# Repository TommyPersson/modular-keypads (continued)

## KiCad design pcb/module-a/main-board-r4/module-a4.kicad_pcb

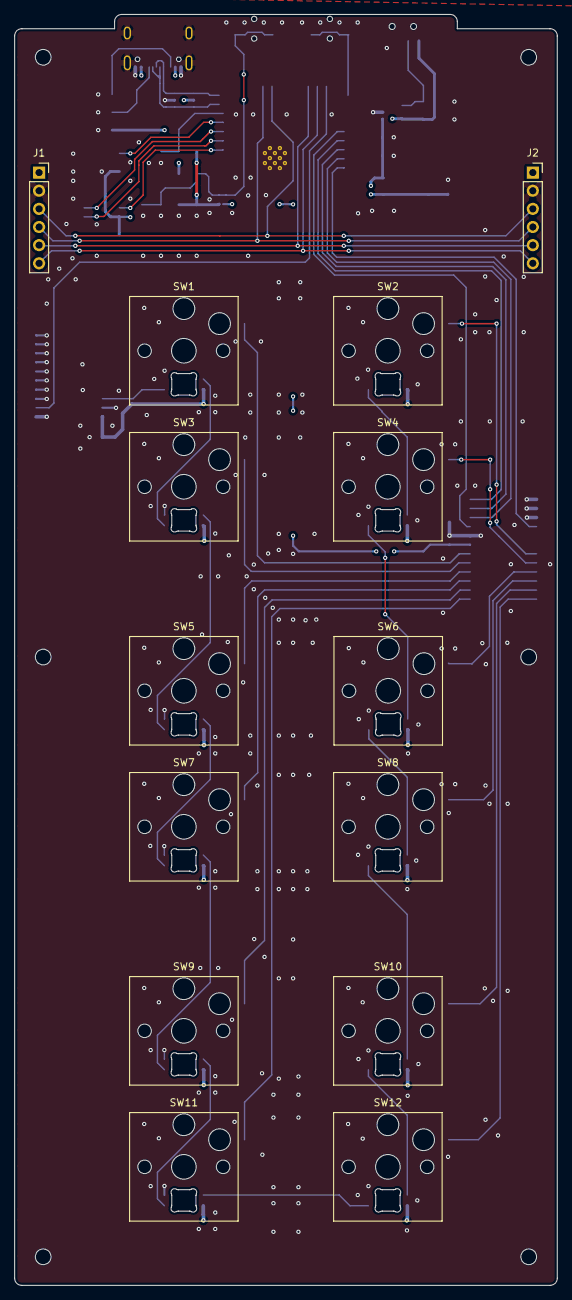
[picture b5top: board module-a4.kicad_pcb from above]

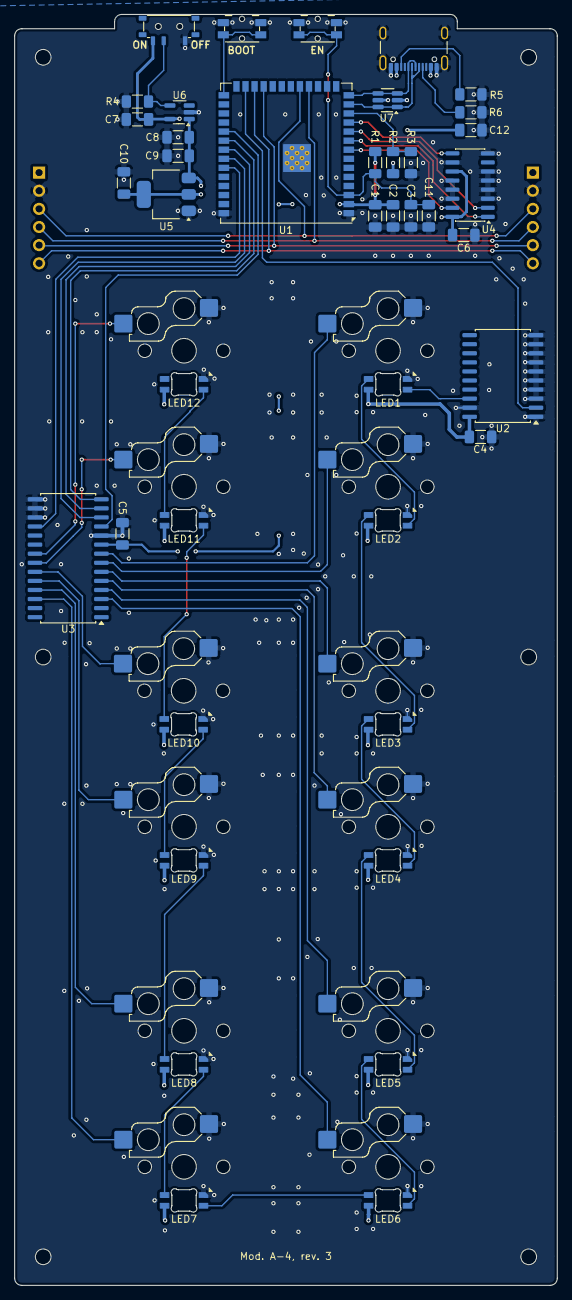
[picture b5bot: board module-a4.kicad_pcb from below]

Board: 4 copper layers, 76.0 x 178.0 mm, 61 parts (41 on the bottom side), 50 nets.

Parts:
C1, C10: 22uF; C_1206_3216Metric_Pad1.33x1.80mm_HandSolder
C2, C4, C5, C6, C7, C8, C11, C12: 0.1uF; C_1206_3216Metric_Pad1.33x1.80mm_HandSolder
C3: 1uF; C_1206_3216Metric_Pad1.33x1.80mm_HandSolder
C9: 10uF; C_1206_3216Metric_Pad1.33x1.80mm_HandSolder
H1, H2, H3, H4, H5, H6: MountingHole; MountingHole_2.2mm_M2
J1: Conn_01x06; PinSocket_1x06_P2.54mm_MagPogoHor_R
J2: Conn_01x06; PinSocket_1x06_P2.54mm_MagPogoHor
J3: USB_C_Receptacle_USB2.0_16P; USB_C_Receptacle_GCT_USB4105-xx-A_16P_TopMnt_Horizontal
LED1, LED2, LED3, LED4, LED5, LED6, LED7, LED8, LED9, LED10, LED11, LED12: SK6812MINI-E; LED_choc_6028R-ROT
R1, R3, R4: 10k; R_1206_3216Metric_Pad1.30x1.75mm_HandSolder
R2: 5.1k; R_1206_3216Metric_Pad1.30x1.75mm_HandSolder
R5, R6: 5.1K; R_1206_3216Metric_Pad1.30x1.75mm_HandSolder
SW1, SW2, SW3, SW4, SW5, SW6, SW7, SW8, SW9, SW10, SW11, SW12: SW_Push; SW_Hotswap_Kailh_Choc_V1_1.50u
SW13: SW_Push_SPDT; SW_MSK12C02-HB
SW14, SW15: SW_Push; Panasonic_EVQPUL_EVQPUC
U1: ESP32-S3-WROOM-1; ESP32-S3-WROOM-1U
U2: 74AHC541; SOIC-20W_7.5x12.8mm_P1.27mm
U3: MCP23S17_SO; SOIC-28W_7.5x17.9mm_P1.27mm
U4: 74HC165; SOIC-16_3.9x9.9mm_P1.27mm
U5: LD1117-3.3H; SOT-223-3_TabPin2
U6: AP2151W; SOT-23-5_HandSoldering
U7: USBLC6-2SC6; SOT-23-6_Handsoldering

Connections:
+3.3V: C1.1, C2.1, C5.1, C6.1, C10.1, R1.1, U1.2 (3V3), U3.9 (VDD), U4.11 (D0), U4.16 (VCC), U5.2 (VO)
+5V: C4.1, C8.1, C9.1, J1.1, J2.1, LED1.1 (VDD), LED2.1 (VDD), LED3.1 (VDD), LED4.1 (VDD), LED5.1 (VDD), LED6.1 (VDD), LED7.1 (VDD), LED8.1 (VDD), LED9.1 (VDD), LED10.1 (VDD), LED11.1 (VDD), LED12.1 (VDD), U2.20 (VCC), U5.3 (VI), U6.1 (OUT)
/A0: SW2.2, U3.21 (GPA0)
/A1: SW4.2, U3.22 (GPA1)
/A2: SW6.2, U3.23 (GPA2)
/A3: SW8.2, U3.24 (GPA3)
/A4: SW10.2, U3.25 (GPA4)
/A5: SW12.2, U3.26 (GPA5)
/B2: SW11.2, U3.3 (GPB2)
/B3: SW9.2, U3.4 (GPB3)
/B4: SW7.2, U3.5 (GPB4)
/B5: SW5.2, U3.6 (GPB5)
/B6: SW3.2, U3.7 (GPB6)
/B7: SW1.2, U3.8 (GPB7)
/EN: C3.1, C11.2, R1.2, SW14.2, U1.3 (EN)
/EX1: J1.5, J2.5, U1.23 (IO21)
/EX2: J1.6, J2.6, U1.24 (IO47)
/IO0: SW15.2, U1.27 (IO0)
/IO48: U1.25 (IO48), U2.2 (A0)
/MISO: U1.32 (IO39), U3.14 (SO)
/MOSI: U1.33 (IO40), U3.13 (SI)
/SCK: U1.34 (IO41), U3.12 (SCK)
/SCL: J1.4, J2.4, U1.18 (IO10)
/SDA: J1.3, J2.3, U1.19 (IO11)
/TREG_CP: U1.10 (IO17), U4.2 (CP)
/TREG_Q: U1.11 (IO18), U4.9 (Q7)
/VBUS_SENSE: R2.2, R3.1, U1.12 (IO8)
/power-distribution/AP_EN: R4.1, SW13.2 (B), U6.4 (EN)
/usb-c-connector/CC1: J3.A5 (CC1), R6.1
/usb-c-connector/CC2: J3.B5 (CC2), R5.1
/~MCP_CS: U1.31 (IO38), U3.11 (~CS)
/~MCP_RESET: U1.35 (IO42), U3.18 (~RESET)
/~TREG_CE: U1.8 (IO15), U4.15 (~CE)
/~TREG_PL: U1.9 (IO16), U4.1 (~PL)
GND: C1.2, C2.2, C3.2, C4.2, C5.2, C6.2, C7.2, C8.2, C9.2, C10.2, C11.1, C12.2, J1.2, J2.2, J3.A1 (GND), J3.A12 (GND), J3.B1 (GND), J3.B12 (GND), J3.S1 (SHIELD), LED1.4 (VSS), LED2.4 (VSS), LED3.4 (VSS), LED4.4 (VSS), LED5.4 (VSS), LED6.4 (VSS), LED7.4 (VSS), LED8.4 (VSS), LED9.4 (VSS), LED10.4 (VSS), LED11.4 (VSS), LED12.4 (VSS), R3.2, R4.2, R5.2, R6.2, SW1.1, SW2.1, SW3.1, SW4.1, SW5.1, SW6.1, SW7.1, SW8.1, SW9.1, SW10.1, SW11.1, SW12.1, SW13.1 (A), SW14.1, SW15.1, U1.1 (GND), U1.40 (GND), U1.41 (GND), U2.1 (G1), U2.3 (A1), U2.4 (A2), U2.5 (A3), U2.6 (A4), U2.7 (A5), U2.8 (A6), U2.9 (A7), U2.10 (GND), U2.19 (G2), U3.10 (VSS), U3.15 (A0), U3.16 (A1), U3.17 (A2), U4.3 (D4), U4.4 (D5), U4.5 (D6), U4.6 (D7), U4.8 (GND), U4.10 (DS), U4.12 (D1), U4.13 (D2), U4.14 (D3), U5.1 (GND), U6.2 (GND), U7.2 (GND)
unnamed: LED1.3 (DIN), U2.18 (Y0)
unnamed: LED1.2 (DOUT), LED2.3 (DIN)
unnamed: LED2.2 (DOUT), LED3.3 (DIN)
unnamed: LED3.2 (DOUT), LED4.3 (DIN)
unnamed: LED4.2 (DOUT), LED5.3 (DIN)
unnamed: LED5.2 (DOUT), LED6.3 (DIN)
unnamed: LED6.2 (DOUT), LED7.3 (DIN)
unnamed: LED7.2 (DOUT), LED8.3 (DIN)
unnamed: LED8.2 (DOUT), LED9.3 (DIN)
unnamed: LED9.2 (DOUT), LED10.3 (DIN)
unnamed: LED10.2 (DOUT), LED11.3 (DIN)
unnamed: LED11.2 (DOUT), LED12.3 (DIN)
USB_D+: J3.A6 (D+), J3.B6 (D+), U1.14 (USB_D+), U7.3 (I/O2), U7.4 (I/O2)
USB_D-: J3.A7 (D-), J3.B7 (D-), U1.13 (USB_D-), U7.1 (I/O1), U7.6 (I/O1)
VBUS: C7.1, C12.1, J3.A4 (VBUS), J3.A9 (VBUS), J3.B4 (VBUS), J3.B9 (VBUS), R2.1, SW13.3 (C), U6.5 (IN), U7.5 (VBUS)
